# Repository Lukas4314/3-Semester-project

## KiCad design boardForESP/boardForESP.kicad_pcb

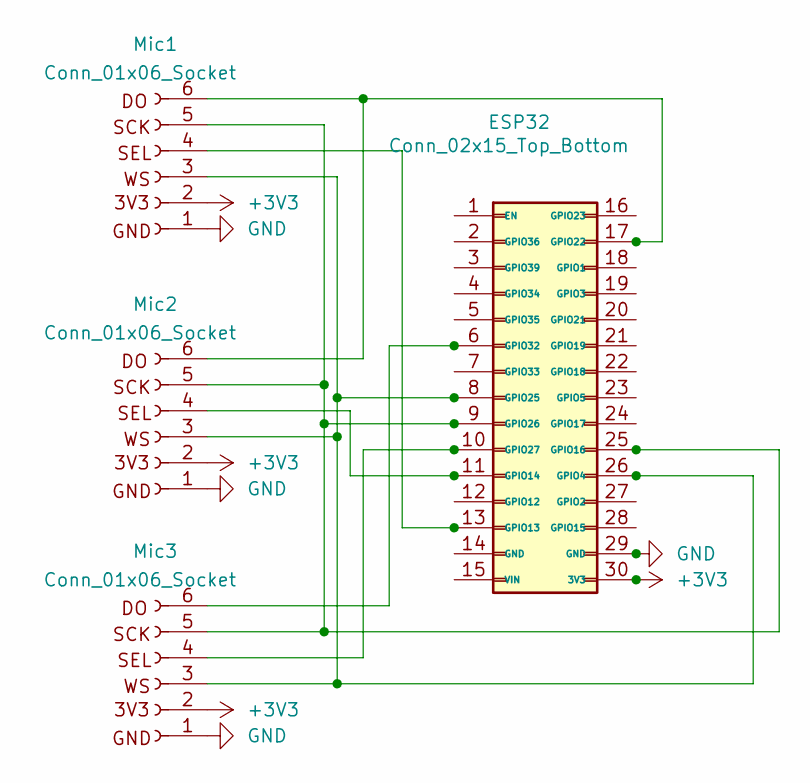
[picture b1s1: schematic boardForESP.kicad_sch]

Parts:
ESP32: Conn_02x15_Top_Bottom; ESP32-C3-DevKitC-02
J1, J2: Conn_01x15_Socket; PinSocket_1x15_P2.54mm_Vertical
Mic1, Mic2, Mic3: Conn_01x06_Socket; PinSocket_1x06_P2.54mm_Vertical

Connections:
+3V3: ESP32.30 (3V3), J2.1, Mic1.2, Mic2.2, Mic3.2
GND: ESP32.29 (GND), J2.2, Mic1.1, Mic2.1, Mic3.1
unnamed: ESP32.1 (EN), J1.15
unnamed: ESP32.18 (GPIO1), J2.13
unnamed: ESP32.27 (GPIO2), J2.4
unnamed: ESP32.19 (GPIO3), J2.12
unnamed: ESP32.23 (GPIO5), J2.8
unnamed: ESP32.12 (GPIO12), J1.4
unnamed: ESP32.13 (GPIO13), J1.3, Mic1.4
unnamed: ESP32.11 (GPIO14), J1.5, Mic2.4
unnamed: ESP32.28 (GPIO15), J2.3
unnamed: ESP32.9 (GPIO26), ESP32.25 (GPIO16), J1.7, J2.6, Mic1.5, Mic2.5, Mic3.5
unnamed: ESP32.24 (GPIO17), J2.7
unnamed: ESP32.22 (GPIO18), J2.9
unnamed: ESP32.21 (GPIO19), J2.10
unnamed: ESP32.20 (GPIO21), J2.11
unnamed: ESP32.17 (GPIO22), J2.14, Mic1.6, Mic2.6
unnamed: ESP32.16 (GPIO23), J2.15
unnamed: ESP32.8 (GPIO25), ESP32.26 (GPIO4), J1.8, J2.5, Mic1.3, Mic2.3, Mic3.3
unnamed: ESP32.10 (GPIO27), J1.6, Mic3.4
unnamed: ESP32.6 (GPIO32), J1.10, Mic3.6
unnamed: ESP32.7 (GPIO33), J1.9
unnamed: ESP32.4 (GPIO34), J1.12
unnamed: ESP32.5 (GPIO35), J1.11
unnamed: ESP32.2 (GPIO36), J1.14
unnamed: ESP32.3 (GPIO39), J1.13
unnamed: ESP32.15 (VIN), J1.1
unnamed: ESP32.14 (GND), J1.2

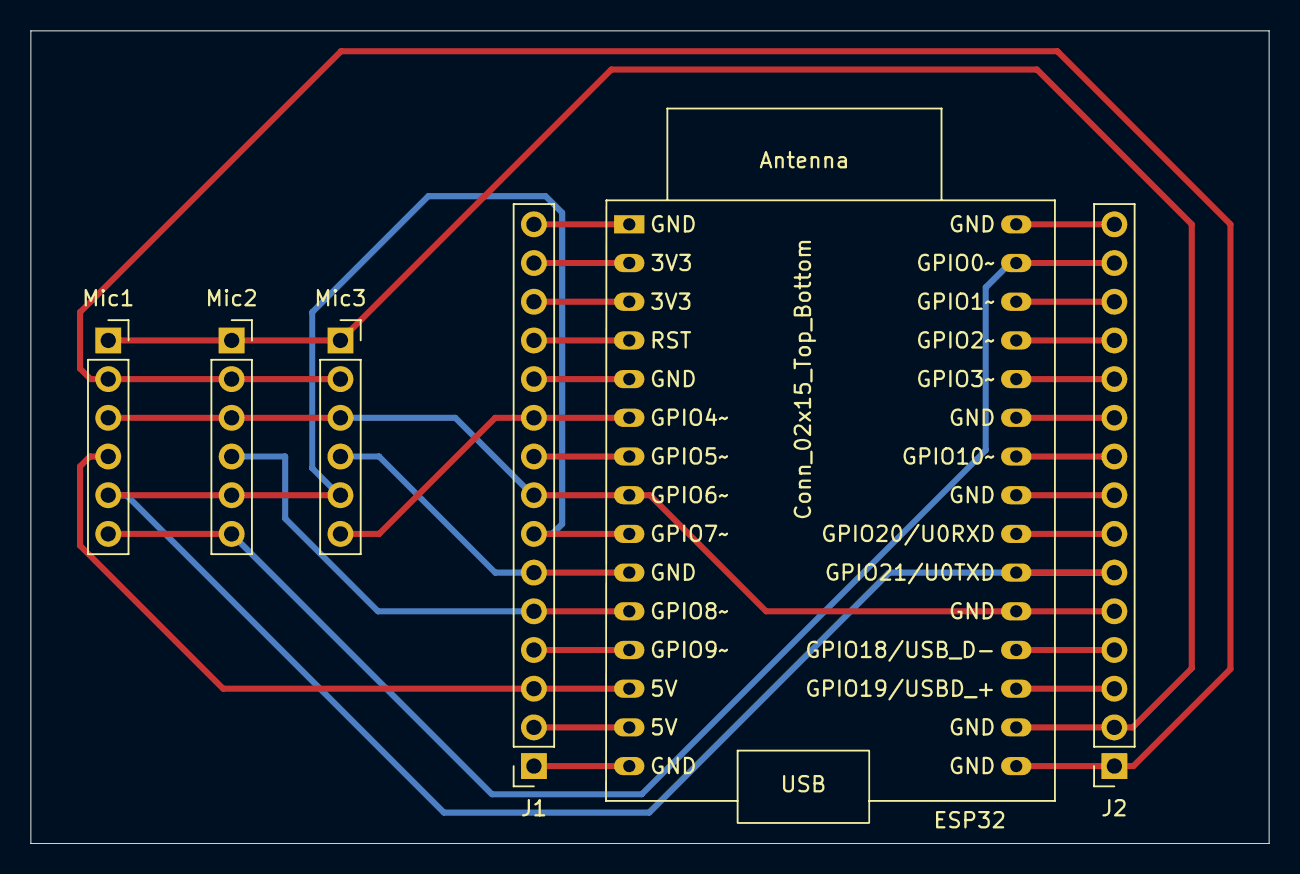
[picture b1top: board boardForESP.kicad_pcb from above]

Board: 2 copper layers, 81.3 x 53.3 mm, 6 parts (0 on the bottom side), 28 nets.

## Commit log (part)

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2025-10-08 made the virt env
2025-10-08 added some more
2025-10-22 with placeholder functions
2025-10-22 turtleController integration
2025-10-22 moved and renamed recording
2025-10-22 improved controller
2025-10-22 added multiple recordings
2025-10-22 Code works with the motors
2025-10-27 added the vibecode
2025-10-27 updated gitignore2
2025-10-27 might work idk
2025-10-27 added sounddevice to init
2025-10-27 fixed error
2025-10-27 added deamon to threading
2025-10-27 added lift to left
2025-10-27 ready for first test, removed default values
2025-10-28 test stuff
2025-10-29 added soundrecordings
2025-10-29 split the code for the turtle bot and the pc code, so now we just pray it works
2025-10-29 made consts.py
2025-11-05 made it work without all the noise
2025-11-05 backup
2025-11-12 it now actually works and we can now talk to the robot
2025-11-12 made test recording and a script to easyli make more
2025-11-19 Added a platformio project
2025-11-19 removed scipy, numpy handles fft
2025-11-26 Make kicad board
2025-11-26 Made it work for a single microphone
2025-11-26 Add JSON configuration for LaTeX tools
2025-11-26 nothingburger
2025-11-26 funky gitignore testing
2025-11-28 lavet tasks.JSON til compile i vscode
2025-12-03 oldrapport
2025-12-03 setting up stuff
2025-12-03 deleted delete
2025-12-03 whisper start
2025-12-03 Telephone band WIP
2025-12-03 Refactor junctions and wires in the schematic for improved connectivity and layout. Added new junctions at specified coordinates and updated wire connections accordingly. Removed redundant junction a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
2025-12-03 gcc_phat now working with filter
2025-12-03 plot kun positive side
2025-12-03 added section files
2025-12-04 Update MQTT server address and enhance audio handling in the main application. Refactor MQTTInterface to support dual audio output queues and improve message processing. Remove lock files and add .gi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
2025-12-04 made improvements to whisper
2025-12-04 implemented come here
2025-12-04 working
2025-12-04 Refactor sound localization and command parsing: - Updated triangulation functions to accept individual TDOA parameters. - Simplified string-to-command mapping for 'come' action. - Enhanced turtle co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
2025-12-05 did some GPU testing on whisper
2025-12-06 added paragraphs to transcribing
2025-12-06 funky stuff
2025-12-06 added sectiontittles to most files
2025-12-06 gccPhat updated after being moved into folder
2025-12-08 Update .gitignore to include additional environment files
2025-12-08 find_best_settings
2025-12-08 lidt optimering
2025-12-08 New triangulate function to make everything hopefully work
2025-12-08 Refactor audio handling and triangulation logic; update microphone positions and improve debugging output
2025-12-09 intergrated the whole system
2025-12-09 Start of sound and identifying commands
2025-12-09 moved bib to bibliography
2025-12-09 trinagulation added
2025-12-09 system setup picture
2025-12-09 added code fom turtbebot
2025-12-10 Refactor code structure for improved readability and maintainability
2025-12-10 sound_recording edited/proofread
2025-12-10 small changes to gccPhat and triangulate that don't matter too much.
2025-12-10 system setup
2025-12-10 Refactor movement control and sound localisation sections; remove redundant test section and enhance transcription explanation
2025-12-10 Add detailed explanation for sound source localization process
2025-12-10 updated discussion
2025-12-11 gcc updated with equations
2025-12-11 Update bibliography entries and enhance command identification section with detailed processing explanation
2025-12-11 Filter
2025-12-11 correlation test gcc phat
2025-12-11 test changed to another test signal simulation
2025-12-11 Add system setup flowchart for Layered Architecture
    - Introduced a comprehensive flowchart in Mermaid format to illustrate the system architecture.
    - Defined three layers: Physical & Comms, Data Processing, and Execution.
    - Detailed components including ESP32, Raspberry Pi, MQTT Broker, and various processing models.
    - Established connections between components to represent data flow and command execution.
2025-12-11 Update sound localisation and system setup descriptions; refine testing results for command identification
2025-12-11 Add flowchart for Raspberry Pi system architecture; update system setup description
2025-12-12 TODO and updated sound localization
2025-12-12 Add WiFi network scanning functionality and logging support; update I2S configurations
2025-12-12 Edited the entire rapport (entire, as of yet)
2025-12-12 z to s
2025-12-12 Updated introduction
2025-12-12 Refactor flowcharts for PC, RPI, and ESP: update labels and add missing connections
2025-12-12 Introduction updated and sound localisation cites source correctly
2025-12-12 Added to discussion
2025-12-12 mqqt changed to mqtt
2025-12-12 Enhance movement control section: add details on command processing and motor regulation
2025-12-13 Start of communication and pub-sub mermaid
2025-12-13 pubsub graph
2025-12-13 added subsecton headers on multiple sections, and updated rpi graph
2025-12-13 Implement SPI slave command handling and update data transfer logic in main.cpp; refactor SPI_test.py for request-per-chunk protocol
2025-12-13 Logger variablenames fixed. Logger almost implemented. The weight and filter/no filter is implemented in gccphatlogging, however samplesize is not implemented
2025-12-13 Lukas look at your citation
2025-12-13 MQTT source added to bibliography and communication moved up to right after system setup
2025-12-13 Interesting, now triangulate doesnt work with the example, probably because the a constants were changed
2025-12-13 Reversed the sign change again... now its correct, now it also prints the error in distance and angle
2025-12-14 Refactor logging constants and improve triangulation functionality
    - Updated logger.py to correct constant names from TDOAPlatWeighting to TDOAPhatWeighting for consistency.
    - Modified triangulate_from_sound function in Triangulate.py to remove unnecessary parameter num_chunks.
    - Adjusted PHAT_GCC_TDOA function in gccPhat.py to use current_samples_size for logging.
    - Enhanced TurtleController class in turtleController.py to streamline microphone data processing and triangulation logic.
    - Simplified SPI data handling in SPI_test.py by replacing manual buffer management with readbytes method.
    - Added initial setup and SPI slave implementation in ESP32-IDF examples and testMain.cpp for better i
2025-12-14 Enhance command extraction and sound localisation descriptions in documentation
2025-12-14 Add SPI communication and I2S audio processing for ESP32
    - Implemented SPI slave functionality in main application to handle audio data transmission.
    - Created I2S interfaces for audio capture from multiple microphones.
    - Developed a Python script for SPI master to query and receive audio packets from ESP32.
    - Added logging for debugging SPI commands and responses.
    - Configured project settings for Python environment in VSCode.
    - Created COLCON_IGNORE file to manage package discovery in the workspace.
2025-12-14 Refine documentation and diagrams for voice-controlled robot project, including clarifications on command interpretation, sound localization, and MQTT broker terminology.
2025-12-15 Refactor sound localisation documentation for clarity and conciseness
2025-12-15 test for movement control ready
2025-12-15 fixed stupid alex code
2025-12-15 Updated graphs, made test table so its ready for data somewhat
2025-12-15 fixed studpid magne code
2025-12-15 Update turtleController and mqtt_2_cmdvel_node for improved control and logging
    - Increased DRIVE_SPEED_M_S from 0.1 to 0.2 in turtleController.
    - Enhanced mqtt_2_cmdvel_node with joint state logging to CSV, including new parameters for acceleration and deceleration profiles.
    - Added error handling for MQTT connections and improved control logic for distance and turn commands.
    - Introduced interpolation for encoder paths and observation data in plotpath.py.
2025-12-15 two figures in sound_localization merged to a side by side and beginning of questions to Toan
2025-12-15 Add drift compensation and logging to mqtt_2_cmdvel_node
2025-12-15 whispertest
2025-12-15 funky stuff, soundtesting.py not working yet
2025-12-16 Questions for Toan
2025-12-16 The questions have been answered
2025-12-16 Triangulate algorithm now uses numpy, so its faster, also its a cylinder now instead of a disk
2025-12-16 Bigger grid, more inaccurate
2025-12-16 Implemented logger in Rune code
2025-12-16 good logs
2025-12-16 Refactor triangulation data analysis to process multiple CSV files from a directory
    - Updated function to analyze all triangulation data from a specified input folder.
    - Enhanced error handling and data extraction for actual angle and distance values.
    - Consolidated results from multiple files into a single DataFrame for comprehensive analysis.
    - Created summary statistics and visualizations for the consolidated data.
    - Added functions for printing key findings and generating a report of the analysis.
    - Improved visualization methods to include performance trends and configuration analysis.
2025-12-16 Implement code changes to enhance functionality and improve performance
2025-12-17 New triangulation image
2025-12-17 Enhance DMA buffer handling and SPI communication for improved data transfer consistency
2025-12-17 New SRP-PHAT discussion
2025-12-17 small fixes on sound_localisation
2025-12-17 Looked detailed at rapport to page 14 and wrote todothings in the todolist.
2025-12-17 added some discussion on sound localisation
2025-12-17 lavet queue på robot. forbedret return logic. fixet double transcipt med en fuld reseter
2025-12-17 bug fixes
2025-12-18 Refactor discussion and testing sections for clarity; adjust figure sizes for better presentation
2025-12-18 hz to Hz
2025-12-18 øøøh
2025-12-18 more funky stuff
2025-12-18 fixing git
2025-12-18 force added find_voice
2025-12-18 updated discussion sound localisation
2025-12-18 Enhance discussion section: clarify movement control, sound localisation, and voice command interface; improve technical details and readability
2025-12-18 Fix typos and improve clarity in discussion and testing sections
2025-12-18 Refine conclusion section to enhance clarity and detail on robot performance and limitations
2025-12-18 Big changes, rapport edited to page 29
2025-12-18 whole rapport edited
2025-12-18 Clarify motor control description in Raspberry Pi architecture
2025-12-18 new front page
2025-12-19 Turned the front page photo and made system setup photo smaller
2025-12-19 new front page photo
2025-12-19 Communication section completed
2025-12-20 Update constants and refactor GCC-PHAT implementation; enable plotting and improve signal handling
2025-12-20 Refactor communication and movement control sections for clarity and consistency
    - Updated the description of MQTT communication in the communication.tex file to enhance clarity and improve technical accuracy.
    - Revised the explanation of MQTT message structure and QoS levels for better understanding.
    - Improved the flow and readability of the movement control section in movement_control.tex, emphasizing the process from human speech to robot movement.
    - Enhanced descriptions of the ROS2 node functionality and the feedback mechanism for motor control.
2025-12-20 funky stuff maybe not good
2025-12-20 Photos are now included in gcc_phat and have bigger label texts
2025-12-21 logmel
2025-12-21 Add sections for Whisper transcription, work distribution, and recordings in the appendix
2025-12-21 Enhance system architecture documentation and improve audio data transfer reliability
2025-12-21 til lille alex
2025-12-21 Fix formatting in work distribution table in appendix
2025-12-21 Refactor transcription section for clarity and structure
2025-12-21 added we to transcriber
2025-12-22 new logmel
2025-12-22 Add sound processing scripts for log-Mel spectrogram computation and triangulation
2025-12-22 Update communication and problem analysis sections for clarity and accuracy
2025-12-22 did some cleaning
2025-12-22 Changes to both spelling, commas, and writing all abbreviations the first time they are used in each section independently
2025-12-22 fixed goofy merge conflict that duplicated a part of a section
2025-12-22 Ændret linjeafstand til 1 i stedet for 1.5, hvilket giver 29 sider i stedet for 41. Hvad synes folket?
2025-12-22 Refactor conclusion and discussion sections for clarity; update sample size in sound localisation tests and append new video examples
2025-12-22 added yap to intro
2025-12-22 new triangulation on real data
2025-12-22 now with TDOA values in the figure
2025-12-22 conclusion checked too now
